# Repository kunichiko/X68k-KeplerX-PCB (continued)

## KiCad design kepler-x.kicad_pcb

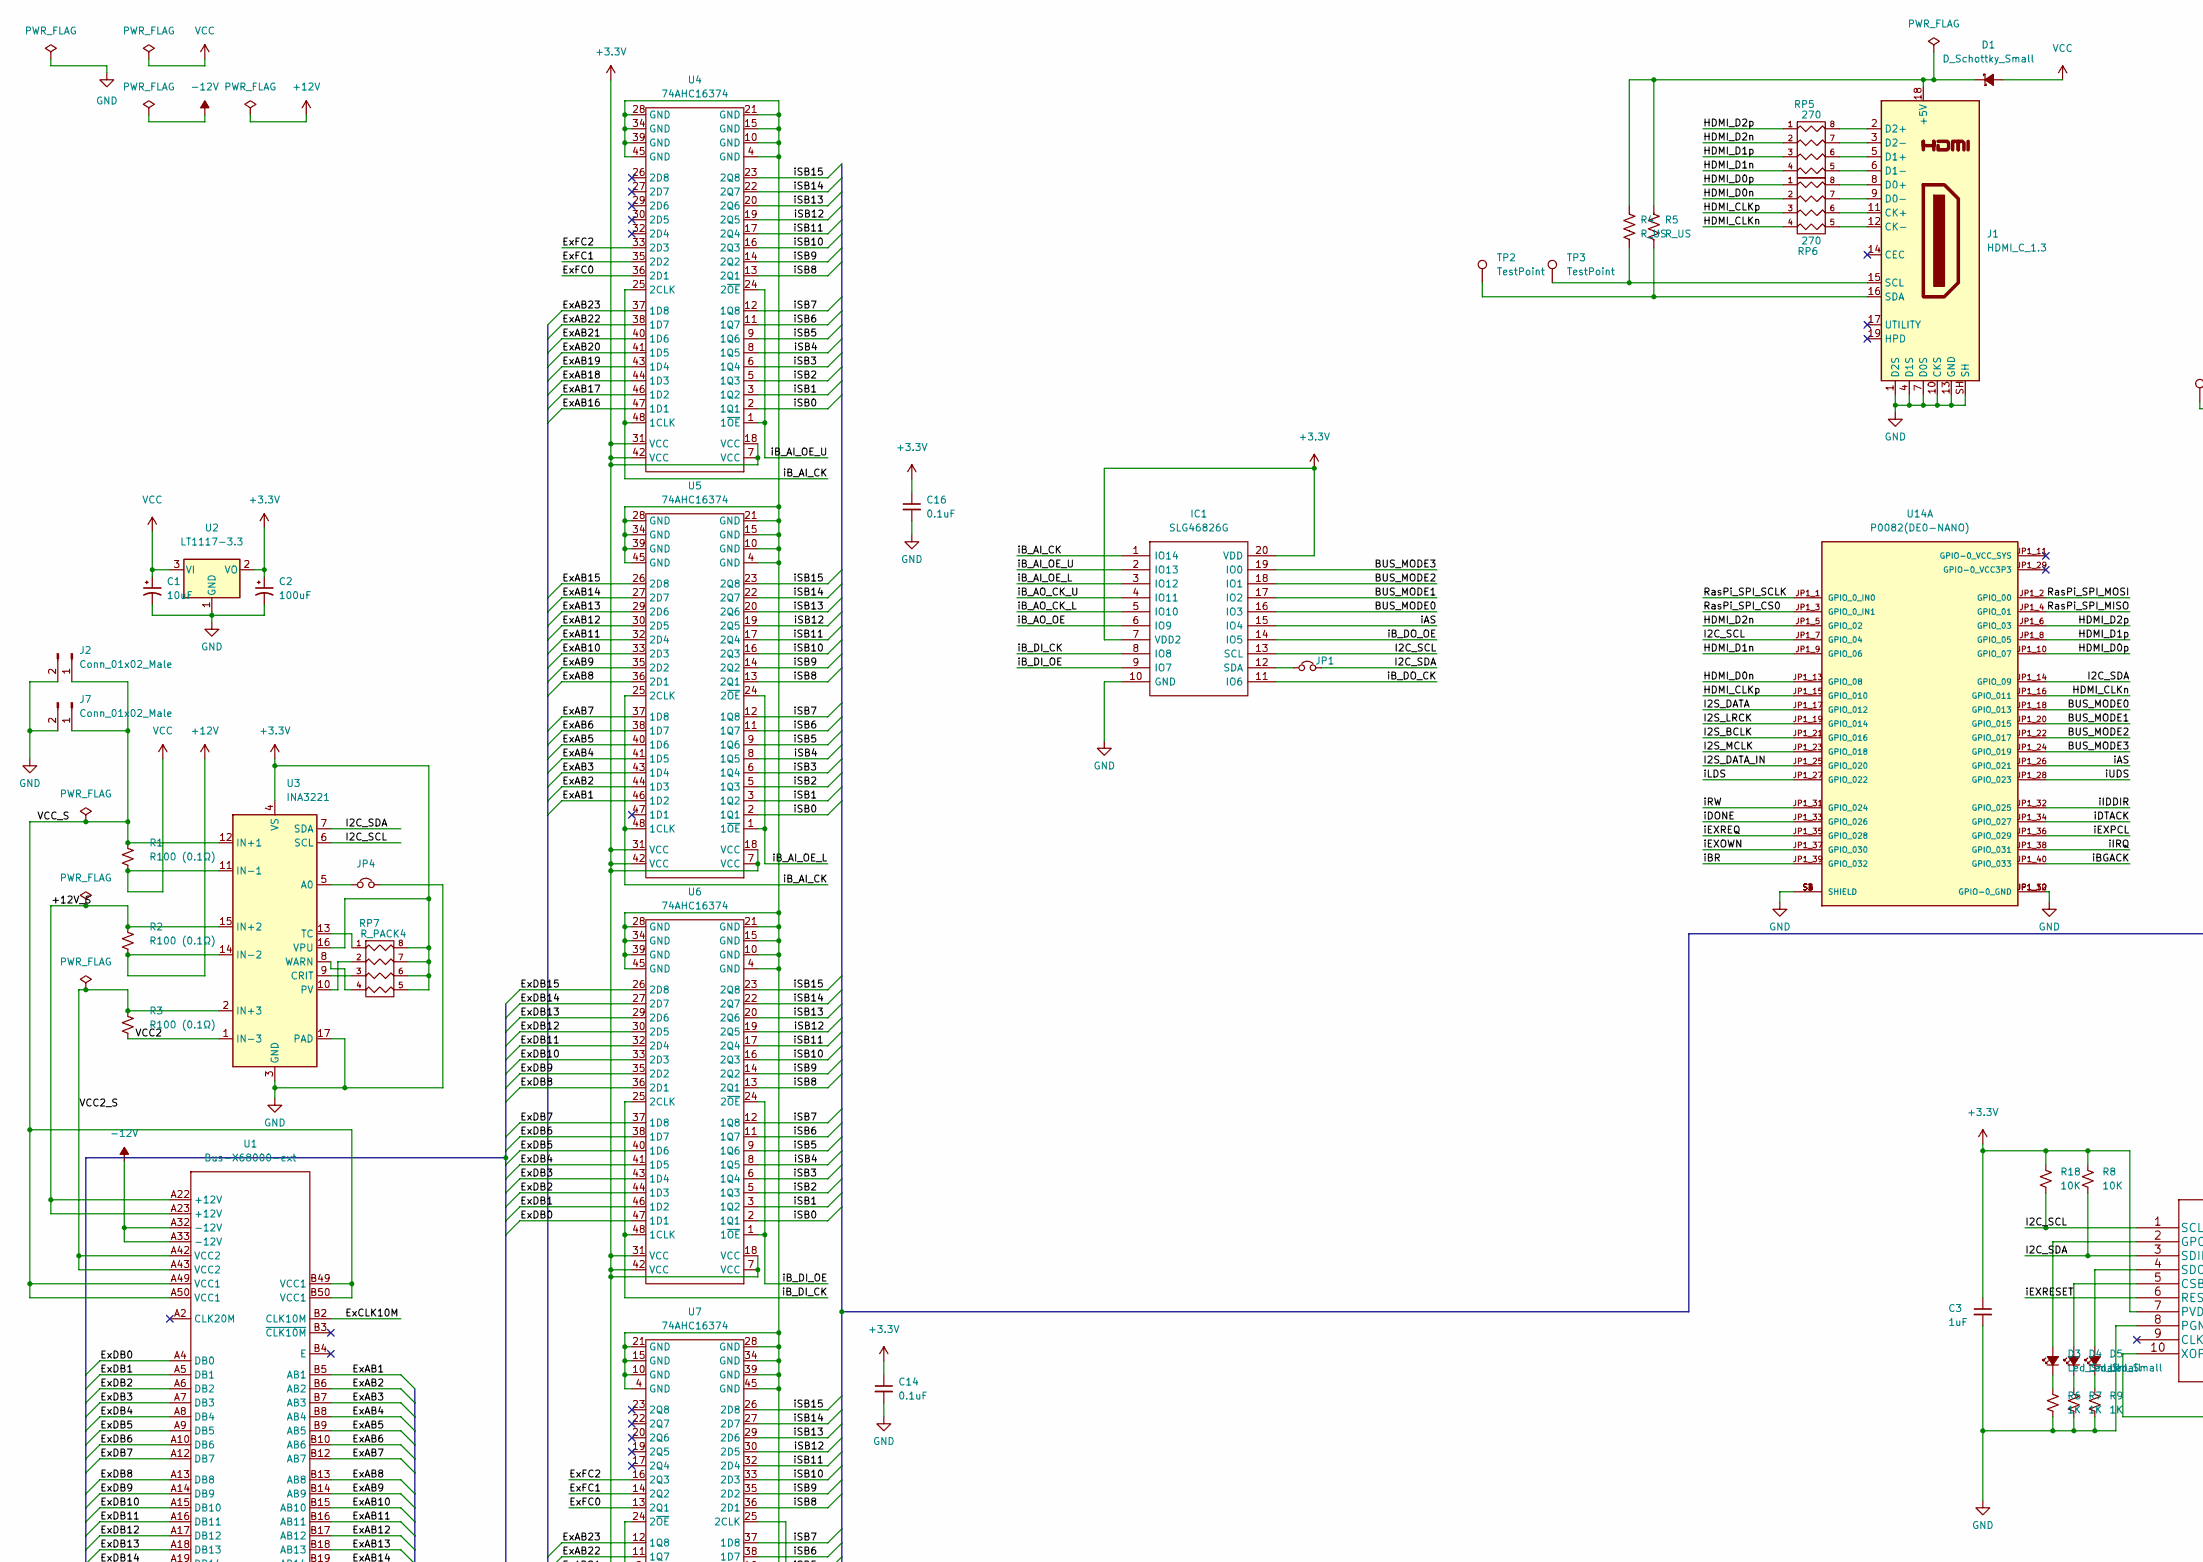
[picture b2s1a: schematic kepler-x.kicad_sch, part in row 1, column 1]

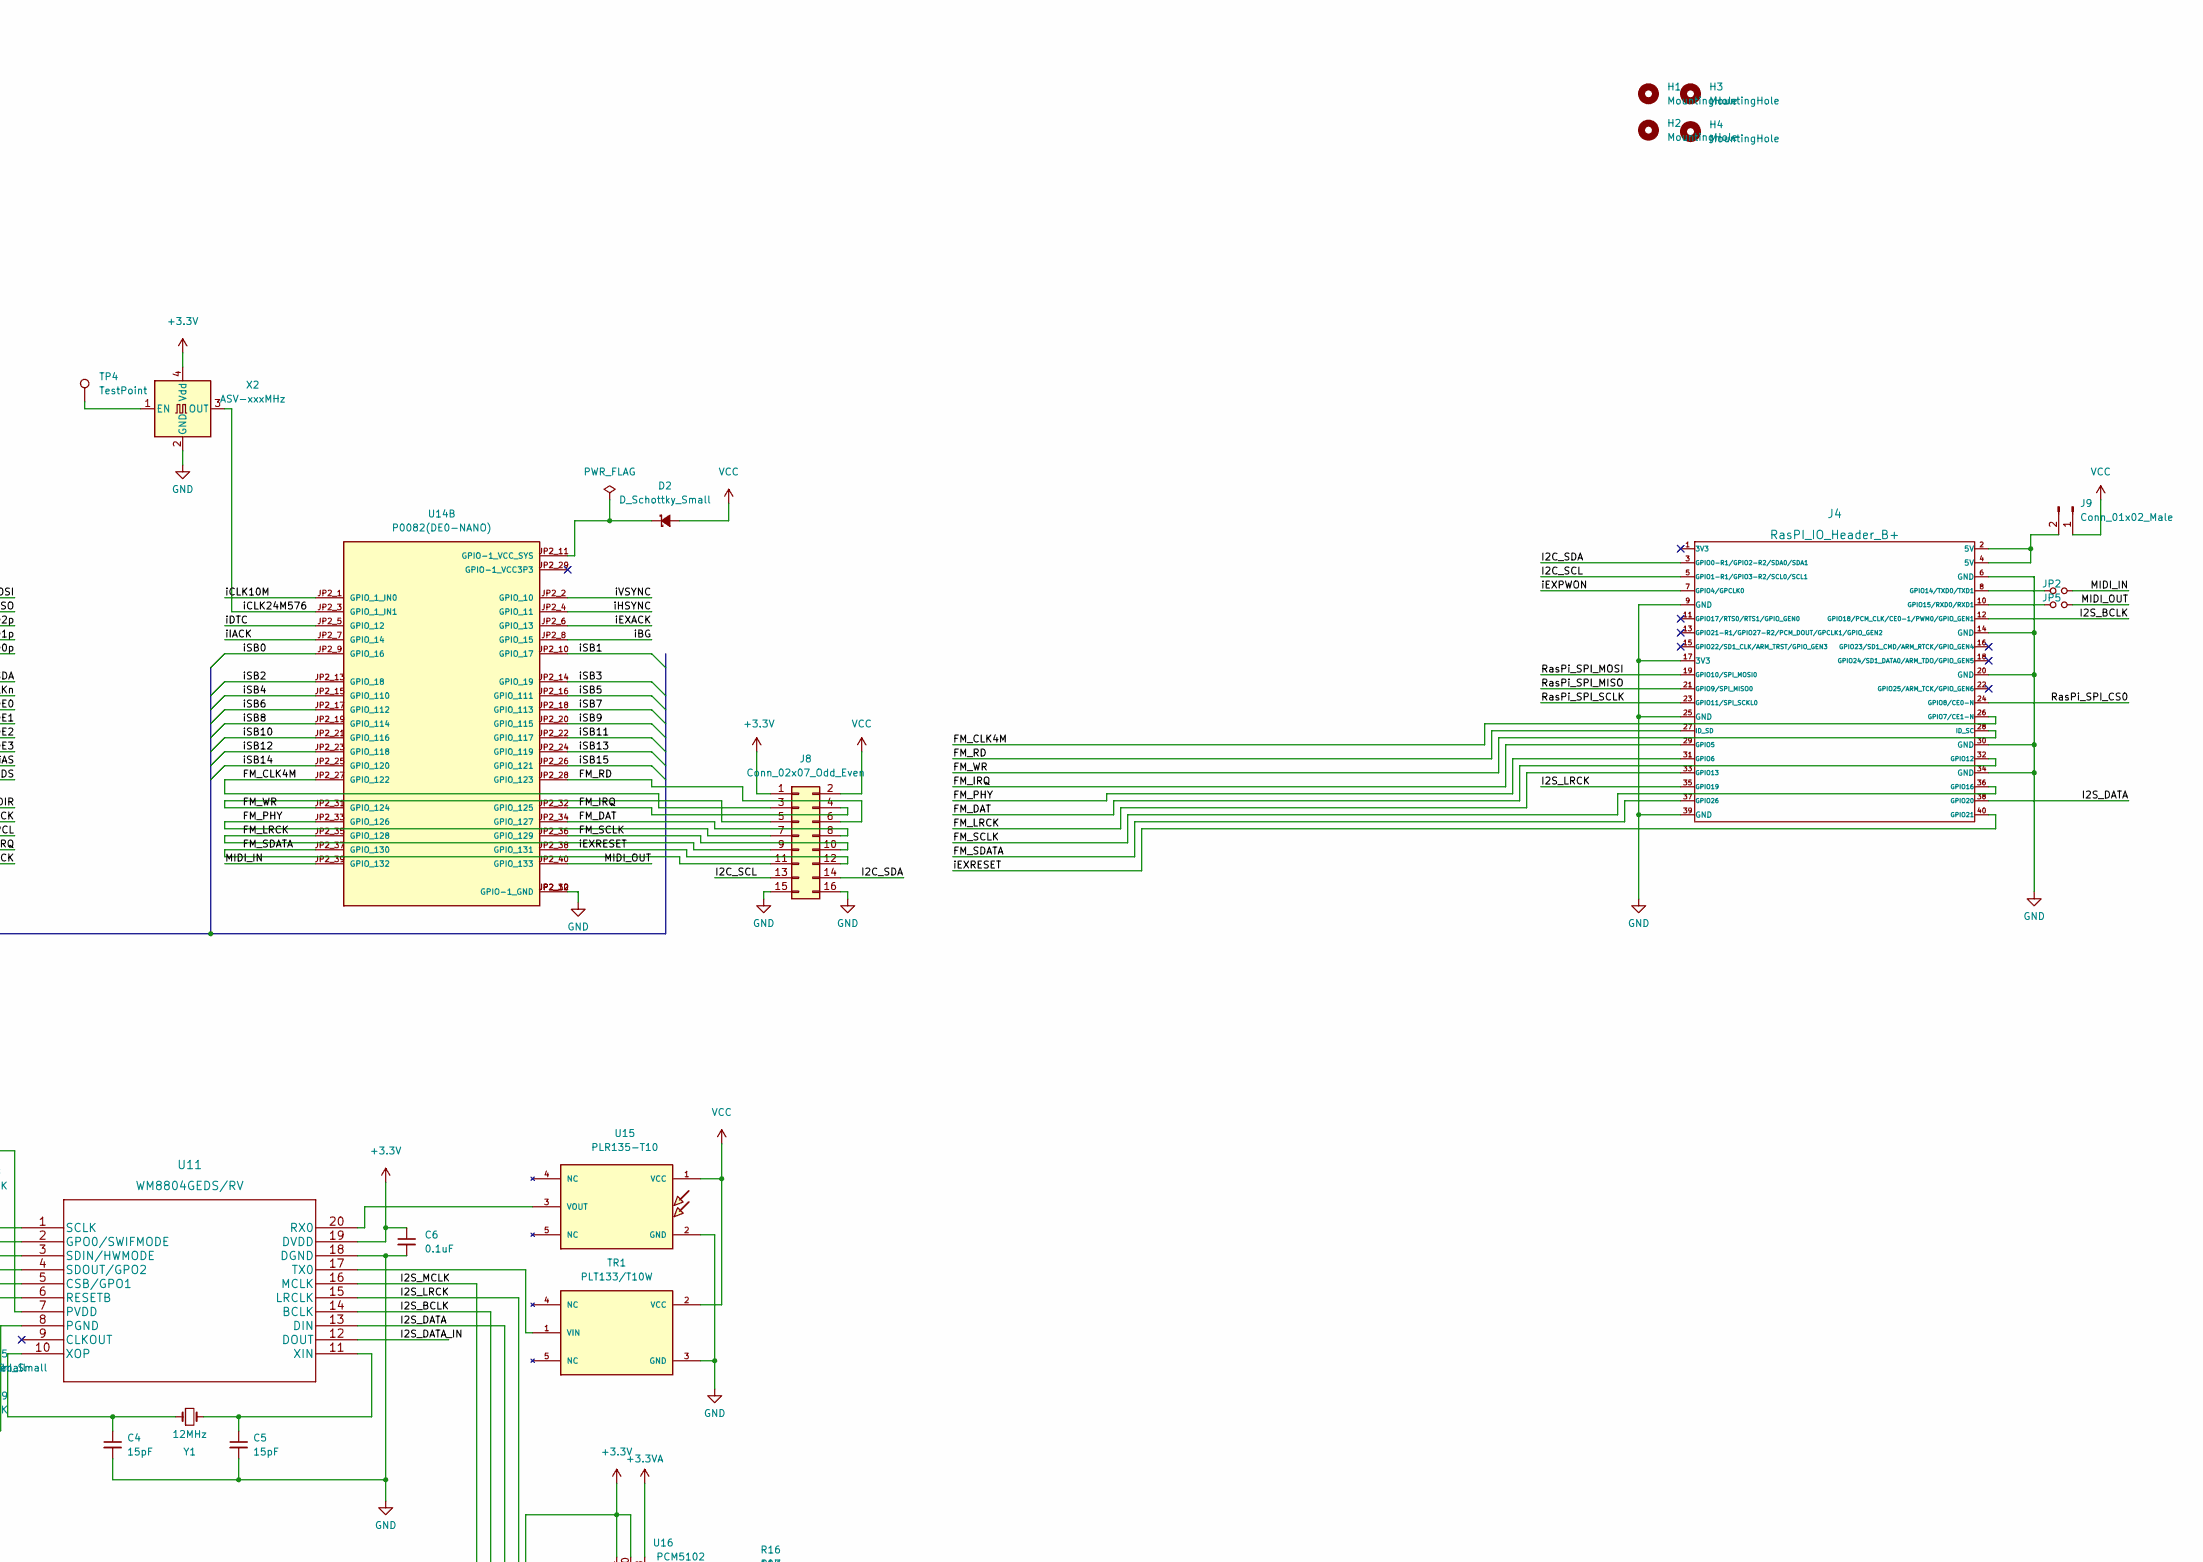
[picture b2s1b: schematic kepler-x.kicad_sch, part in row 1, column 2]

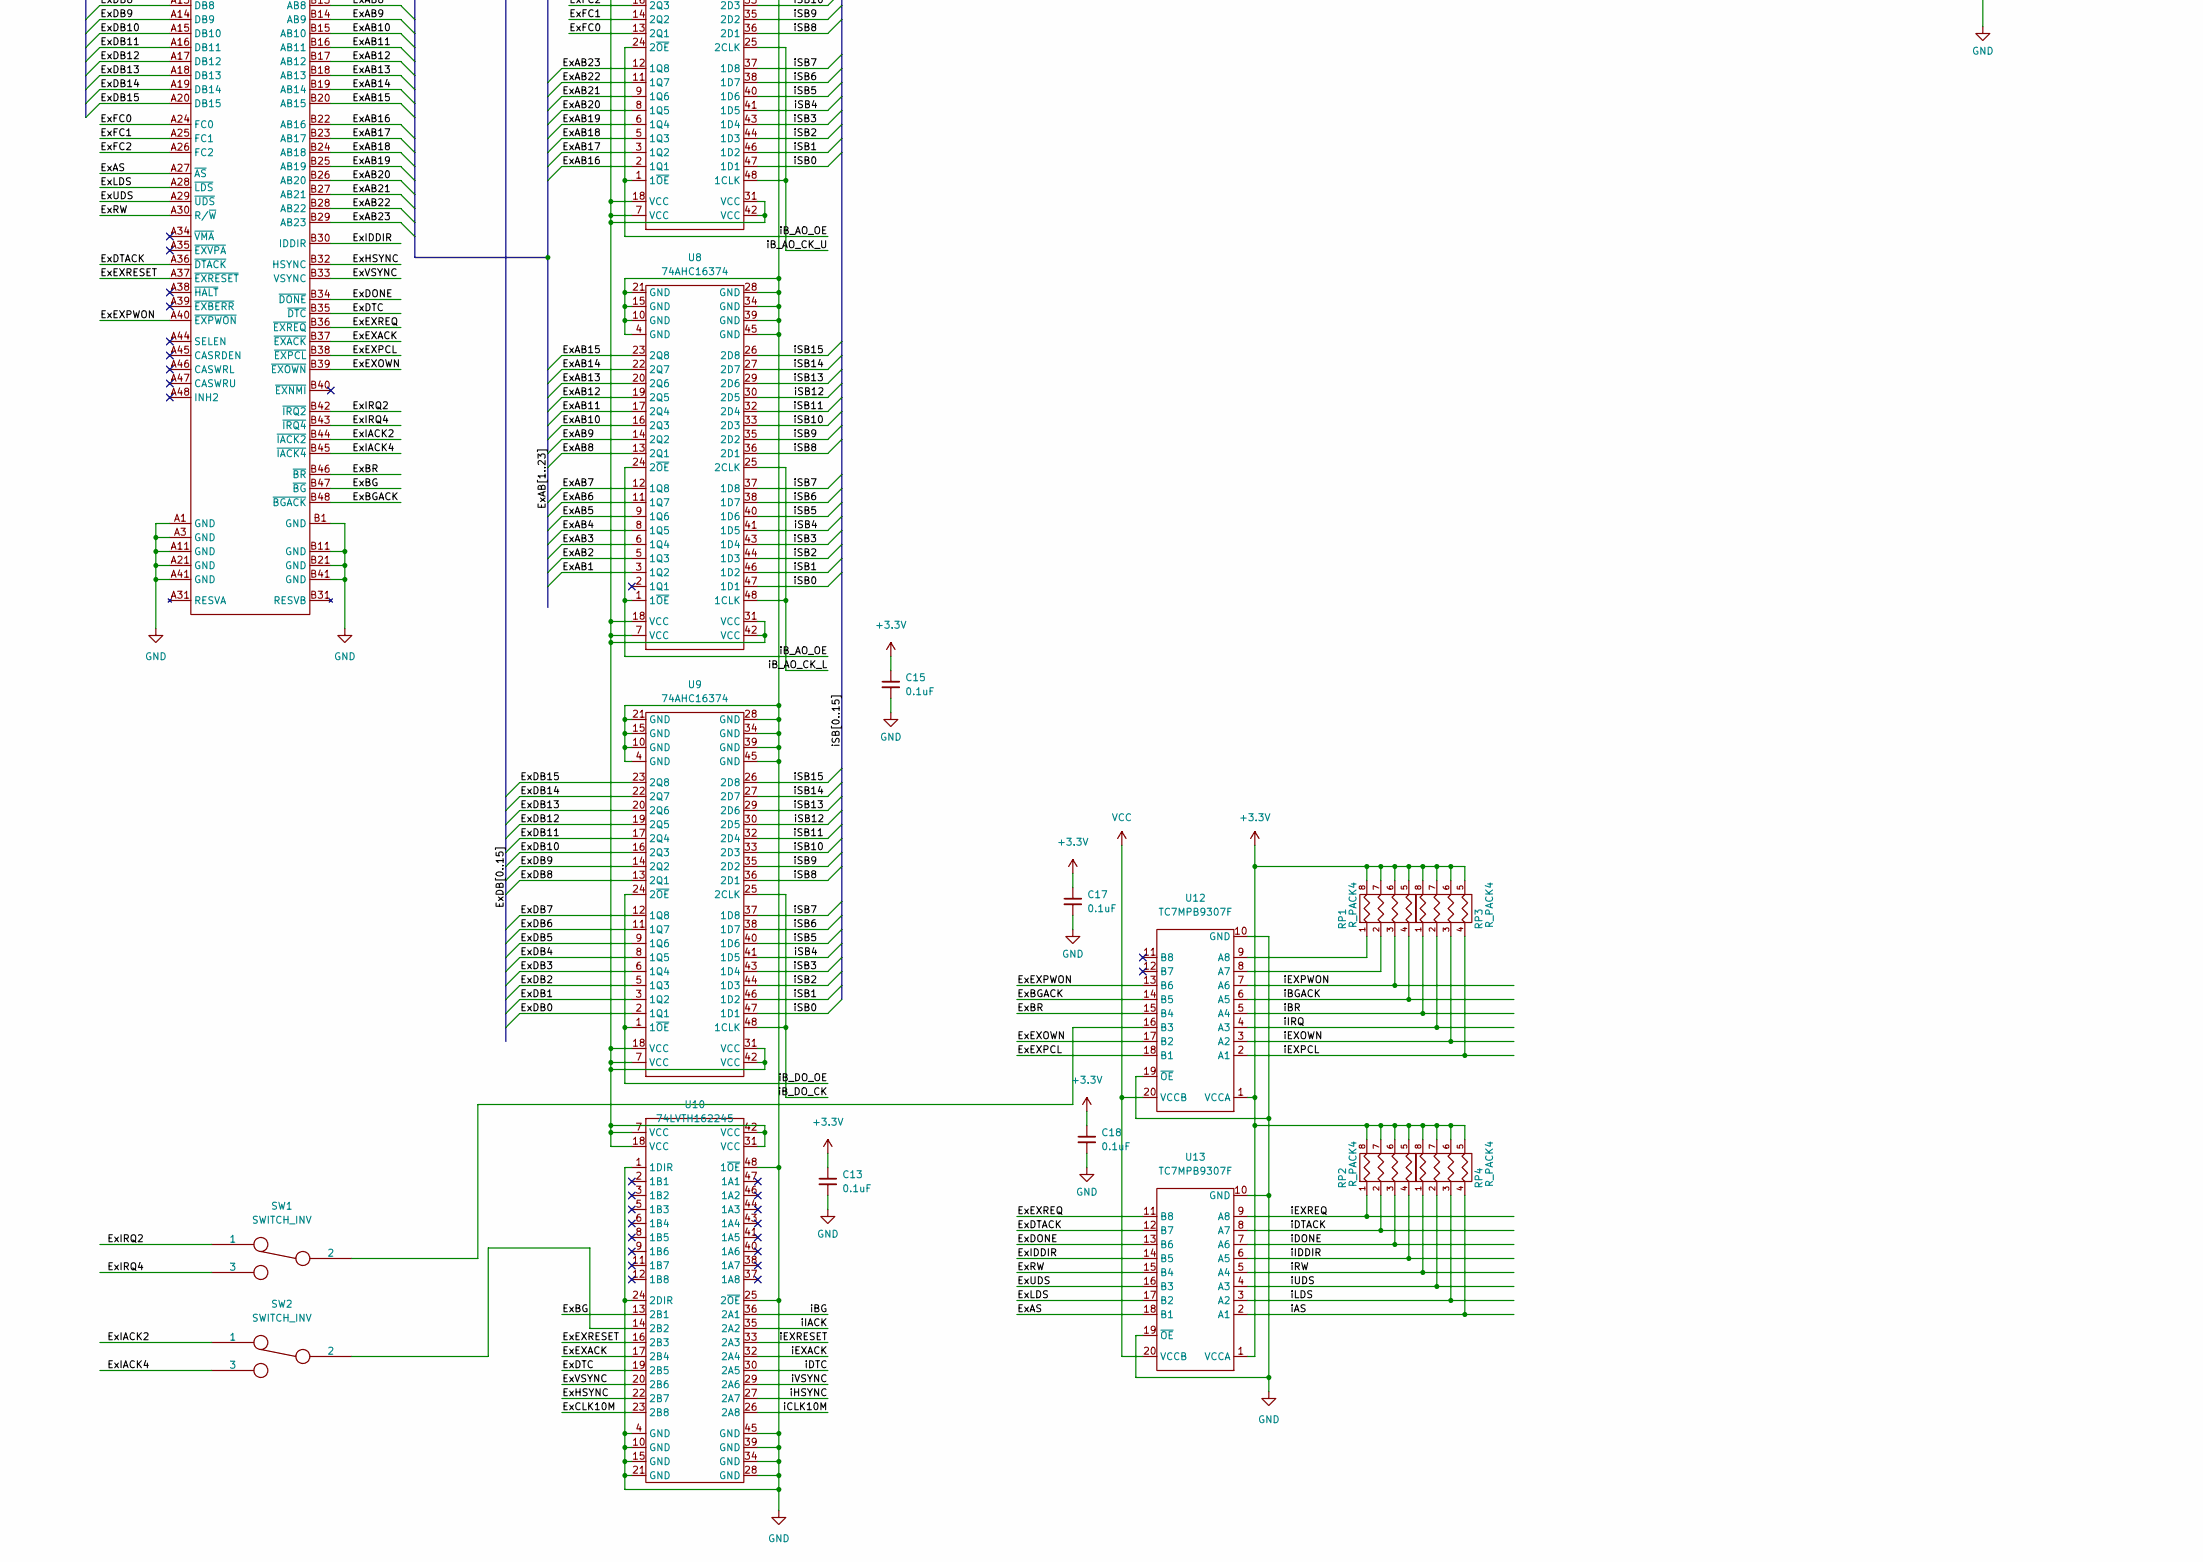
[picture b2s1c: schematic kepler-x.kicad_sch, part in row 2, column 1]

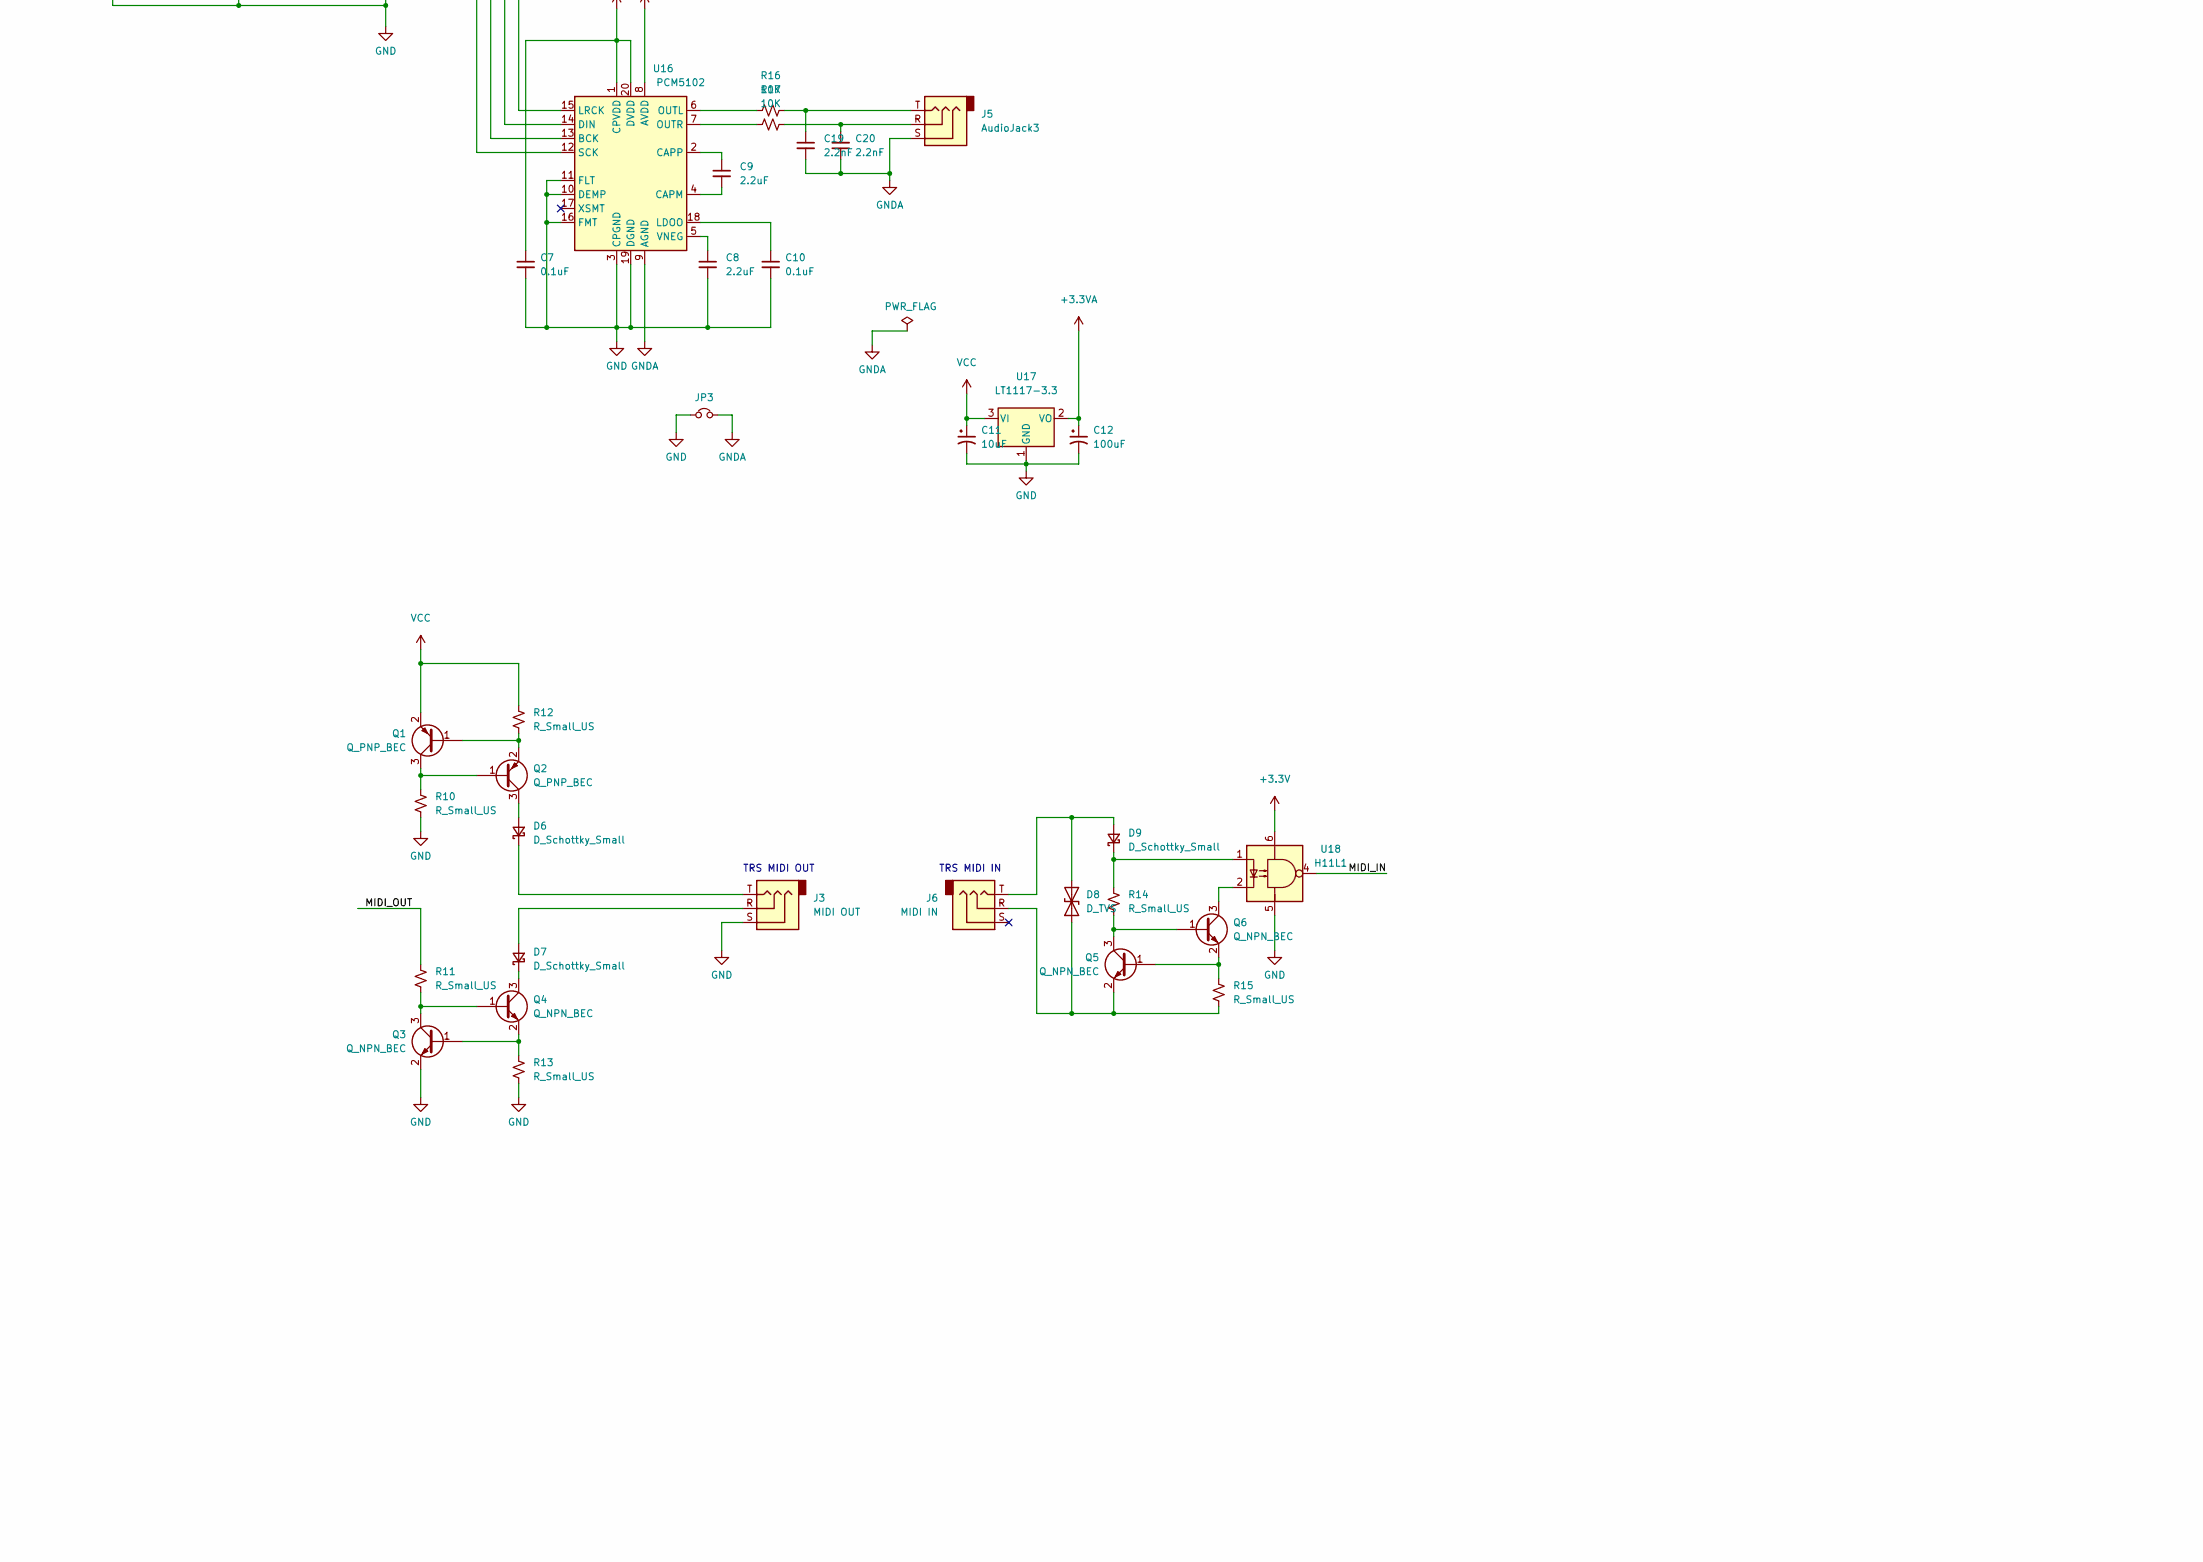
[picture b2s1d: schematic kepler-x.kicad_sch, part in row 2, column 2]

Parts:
C1, C11: 10uF; CP_Radial_D5.0mm_P2.50mm
C2, C12: 100uF; CP_Radial_D5.0mm_P2.50mm
C3: 1uF; C_0603_1608Metric_Pad1.08x0.95mm_HandSolder
C4, C5: 15pF; C_0603_1608Metric_Pad1.08x0.95mm_HandSolder
C6, C7, C10, C13, C14, C15, C16, C17, C18: 0.1uF; C_0603_1608Metric_Pad1.08x0.95mm_HandSolder
C8, C9: 2.2uF; C_0603_1608Metric_Pad1.08x0.95mm_HandSolder
C19, C20: 2.2nF; C_0603_1608Metric_Pad1.08x0.95mm_HandSolder
D1, D2, D6, D7, D9: D_Schottky_Small; D_1206_3216Metric_Pad1.42x1.75mm_HandSolder
D3, D4, D5: Led_Small; LED_0603_1608Metric_Pad1.05x0.95mm_HandSolder
D8: D_TVS; D_1206_3216Metric_Pad1.42x1.75mm_HandSolder
H1, H2: MountingHole; MountingHole_3.7mm
H3, H4: MountingHole; MountingHole_2.7mm_M2.5
IC1: SLG46826G; SOP65P640X120-20N; Manufacturer_Part_Number SLG46826G
J1: HDMI_C_1.3; HDMI_Mini_Female_2001-1-2-21-00-BK
J2, J7, J9: Conn_01x02_Male; PinHeader_1x02_P2.54mm_Vertical
J3: MIDI OUT; Jack_3.5mm_Switronic_ST-005-G_horizontal
J4: RasPI_IO_Header_B+; Raspberry_Pi_Zero_Socketed_THT_FaceDown_MountingHoles
J5: AudioJack3; Jack_3.5mm_Switronic_ST-005-G_horizontal
J6: MIDI IN; Jack_3.5mm_Switronic_ST-005-G_horizontal
J8: Conn_02x07_Odd_Even; PinHeader_2x08_P2.54mm_Vertical
JP1: Jumper_NC_Small; PinHeader_1x2_P2.54mm
JP2, JP5: Jumper_NO_Small; SolderJumper-2_P1.3mm_Open_RoundedPad1.0x1.5mm
JP3, JP4: Jumper_NC_Small; SolderJumper-2_P1.3mm_Bridged_RoundedPad1.0x1.5mm
Q1, Q2: Q_PNP_BEC; SC-59_Handsoldering
Q3, Q4, Q5, Q6: Q_NPN_BEC; SC-59_Handsoldering
R1, R2, R3: R100 (0.1Ω); R_2512_6332Metric_Pad1.40x3.35mm_HandSolder
R4, R5: R_US; R_0603_1608Metric_Pad0.98x0.95mm_HandSolder
R6, R7, R9: 1K; R_0603_1608Metric_Pad0.98x0.95mm_HandSolder
R8, R16, R17, R18: 10K; R_0603_1608Metric_Pad0.98x0.95mm_HandSolder
R10, R11, R12, R13, R14, R15: R_Small_US; R_0603_1608Metric_Pad0.98x0.95mm_HandSolder
RP1, RP2, RP3, RP4, RP7: R_PACK4; R_Array_Convex_4x0603
RP5, RP6: 270; R_Array_Convex_4x0603
SW1, SW2: SWITCH_INV; Pin_Header_Straight_1x03
TP2, TP3, TP4: TestPoint; TestPoint_THTPad_2.0x2.0mm_Drill1.0mm
TR1: PLT133/T10W; XDCR_PLT133_T10W; PARTREV 5
U1: Bus-X68000-ext; x68000-ext-cardedge
U2, U17: LT1117-3.3; SOT-223-3_TabPin2
U3: INA3221; QFN-16-1EP_4x4mm_Pitch0.65mm
U4, U5, U6, U7, U8, U9: 74AHC16374; SSOP-48_7.5x15.9mm_Pitch0.635mm
U10: 74LVTH162245; SSOP-48_7.5x15.9mm_Pitch0.635mm
U11: WM8804GEDS/RV; WM8804GEDS&slash_RV
U12, U13: TC7MPB9307F; TSSOP-20_4.4x6.5mm_Pitch0.65mm
U14: P0082(DE0-NANO); MODULE_P0082_TOPMOUNT; PARTREV V2.0
U15: PLR135-T10; XDCR_PLT133_T10W
U16: PCM5102; TSSOP-20_4.4x6.5mm_P0.65mm
U18: H11L1; DIP-6_W7.62mm
X2: ASV-xxxMHz; Oscillator_SMD_Abracon_ASV-4Pin_7.0x5.1mm
Y1: 12MHz; Crystal_HC49-U_Vertical

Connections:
+3.3VA: C12.1, U16.8 (AVDD), U17.2 (VO)
+3V3: C2.1, C3.1, C6.1, C7.1, C13.1, C14.1, C15.1, C16.1, C17.1, C18.1, IC1.7 (VDD2), IC1.20 (VDD), J8.1, R8.1, R18.1, RP1.5 (R4), RP1.6 (R3), RP1.7 (R2), RP1.8 (R1), RP2.5 (R4), RP2.6 (R3), RP2.7 (R2), RP2.8 (R1), RP3.5 (R4), RP3.6 (R3), RP3.7 (R2), RP3.8 (R1), RP4.5 (R4), RP4.6 (R3), RP4.7 (R2), RP4.8 (R1), RP7.5 (R4), RP7.6 (R3), RP7.7 (R2), RP7.8 (R1), U2.2 (VO), U3.4 (VS), U3.16 (VPU), U4.7 (VCC), U4.18 (VCC), U4.31 (VCC), U4.42 (VCC), U5.7 (VCC), U5.18 (VCC), U5.31 (VCC), U5.42 (VCC), U6.7 (VCC), U6.18 (VCC), U6.31 (VCC), U6.42 (VCC), U7.7 (VCC), U7.18 (VCC), U7.31 (VCC), U7.42 (VCC), U8.7 (VCC), U8.18 (VCC), U8.31 (VCC), U8.42 (VCC), U9.7 (VCC), U9.18 (VCC), U9.31 (VCC), U9.42 (VCC), U10.7 (VCC), U10.18 (VCC), U10.31 (VCC), U10.42 (VCC), U11.7 (PVDD), U11.19 (DVDD), U12.1 (VCCA), U13.1 (VCCA), U16.1 (CPVDD), U16.20 (DVDD), U18.6, X2.4 (Vdd)
+12V: R2.2, U3.14 (IN-2)
-12V: U1.A32 (-12V), U1.A33 (-12V)
/+12V_S: R2.1, U1.A22 (+12V), U1.A23 (+12V), U3.15 (IN+2)
/BUS_MODE0: IC1.16 (IO3), U14.JP1_18 (GPIO_013)
/BUS_MODE1: IC1.17 (IO2), U14.JP1_20 (GPIO_015)
/BUS_MODE2: IC1.18 (IO1), U14.JP1_22 (GPIO_017)
/BUS_MODE3: IC1.19 (IO0), U14.JP1_24 (GPIO_019)
/ExAB1: U1.B5 (AB1), U5.46 (1D2), U8.3 (1Q2)
/ExAB2: U1.B6 (AB2), U5.44 (1D3), U8.5 (1Q3)
/ExAB3: U1.B7 (AB3), U5.43 (1D4), U8.6 (1Q4)
/ExAB4: U1.B8 (AB4), U5.41 (1D5), U8.8 (1Q5)
/ExAB5: U1.B9 (AB5), U5.40 (1D6), U8.9 (1Q6)
/ExAB6: U1.B10 (AB6), U5.38 (1D7), U8.11 (1Q7)
/ExAB7: U1.B12 (AB7), U5.37 (1D8), U8.12 (1Q8)
/ExAB8: U1.B13 (AB8), U5.36 (2D1), U8.13 (2Q1)
/ExAB9: U1.B14 (AB9), U5.35 (2D2), U8.14 (2Q2)
/ExAB10: U1.B15 (AB10), U5.33 (2D3), U8.16 (2Q3)
/ExAB11: U1.B16 (AB11), U5.32 (2D4), U8.17 (2Q4)
/ExAB12: U1.B17 (AB12), U5.30 (2D5), U8.19 (2Q5)
/ExAB13: U1.B18 (AB13), U5.29 (2D6), U8.20 (2Q6)
/ExAB14: U1.B19 (AB14), U5.27 (2D7), U8.22 (2Q7)
/ExAB15: U1.B20 (AB15), U5.26 (2D8), U8.23 (2Q8)
/ExAB16: U1.B22 (AB16), U4.47 (1D1), U7.2 (1Q1)
/ExAB17: U1.B23 (AB17), U4.46 (1D2), U7.3 (1Q2)
/ExAB18: U1.B24 (AB18), U4.44 (1D3), U7.5 (1Q3)
/ExAB19: U1.B25 (AB19), U4.43 (1D4), U7.6 (1Q4)
/ExAB20: U1.B26 (AB20), U4.41 (1D5), U7.8 (1Q5)
/ExAB21: U1.B27 (AB21), U4.40 (1D6), U7.9 (1Q6)
/ExAB22: U1.B28 (AB22), U4.38 (1D7), U7.11 (1Q7)
/ExAB23: U1.B29 (AB23), U4.37 (1D8), U7.12 (1Q8)
/ExAS: U1.A27 (~AS), U13.18 (B1)
/ExBG: U1.B47 (~BG), U10.13 (2B1)
/ExBGACK: U1.B48 (~BGACK), U12.14 (B5)
/ExBR: U1.B46 (~BR), U12.15 (B4)
/ExCLK10M: U1.B2 (CLK10M), U10.23 (2B8)
/ExDB0: U1.A4 (DB0), U6.47 (1D1), U9.2 (1Q1)
/ExDB1: U1.A5 (DB1), U6.46 (1D2), U9.3 (1Q2)
/ExDB2: U1.A6 (DB2), U6.44 (1D3), U9.5 (1Q3)
/ExDB3: U1.A7 (DB3), U6.43 (1D4), U9.6 (1Q4)
/ExDB4: U1.A8 (DB4), U6.41 (1D5), U9.8 (1Q5)
/ExDB5: U1.A9 (DB5), U6.40 (1D6), U9.9 (1Q6)
/ExDB6: U1.A10 (DB6), U6.38 (1D7), U9.11 (1Q7)
/ExDB7: U1.A12 (DB7), U6.37 (1D8), U9.12 (1Q8)
/ExDB8: U1.A13 (DB8), U6.36 (2D1), U9.13 (2Q1)
/ExDB9: U1.A14 (DB9), U6.35 (2D2), U9.14 (2Q2)
/ExDB10: U1.A15 (DB10), U6.33 (2D3), U9.16 (2Q3)
/ExDB11: U1.A16 (DB11), U6.32 (2D4), U9.17 (2Q4)
/ExDB12: U1.A17 (DB12), U6.30 (2D5), U9.19 (2Q5)
/ExDB13: U1.A18 (DB13), U6.29 (2D6), U9.20 (2Q6)
/ExDB14: U1.A19 (DB14), U6.27 (2D7), U9.22 (2Q7)
/ExDB15: U1.A20 (DB15), U6.26 (2D8), U9.23 (2Q8)
/ExDONE: U1.B34 (~DONE), U13.13 (B6)
/ExDTACK: U1.A36 (~DTACK), U13.12 (B7)
/ExDTC: U1.B35 (~DTC), U10.19 (2B5)
/ExEXACK: U1.B37 (~EXACK), U10.17 (2B4)
/ExEXOWN: U1.B39 (~EXOWN), U12.17 (B2)
/ExEXPCL: U1.B38 (~EXPCL), U12.18 (B1)
/ExEXPWON: U1.A40 (~EXPWON), U12.13 (B6)
/ExEXREQ: U1.B36 (~EXREQ), U13.11 (B8)
/ExEXRESET: U1.A37 (~EXRESET), U10.16 (2B3)
/ExFC0: U1.A24 (FC0), U4.36 (2D1), U7.13 (2Q1)
/ExFC1: U1.A25 (FC1), U4.35 (2D2), U7.14 (2Q2)
/ExFC2: U1.A26 (FC2), U4.33 (2D3), U7.16 (2Q3)
/ExHSYNC: U1.B32 (HSYNC), U10.22 (2B7)
/ExIACK2: SW2.1, U1.B44 (~IACK2)
/ExIACK4: SW2.3, U1.B45 (~IACK4)
/ExIDDIR: U1.B30 (IDDIR), U13.14 (B5)
/ExIRQ2: SW1.1, U1.B42 (~IRQ2)
/ExIRQ4: SW1.3, U1.B43 (~IRQ4)
/ExLDS: U1.A28 (~LDS), U13.17 (B2)
/ExRW: U1.A30 (R/~W), U13.15 (B4)
/ExUDS: U1.A29 (~UDS), U13.16 (B3)
/ExVSYNC: U1.B33 (VSYNC), U10.20 (2B6)
/FM_CLK4M: J4.26 (GPIO7/CE1-N), J8.3, U14.JP2_27 (GPIO_122)
/FM_DAT: J4.32 (GPIO12), J8.8, U14.JP2_34 (GPIO_127)
/FM_IRQ: J4.29 (GPIO5), J8.4, U14.JP2_32 (GPIO_125)
/FM_LRCK: J4.33 (GPIO13), J8.9, U14.JP2_35 (GPIO_128)
/FM_PHY: J4.31 (GPIO6), J8.7, U14.JP2_33 (GPIO_126)
/FM_RD: J4.27 (ID_SD), J8.6, U14.JP2_28 (GPIO_123)
/FM_SCLK: J4.36 (GPIO16), J8.10, U14.JP2_36 (GPIO_129)
/FM_SDATA: J4.37 (GPIO26), J8.11, U14.JP2_37 (GPIO_130)
/FM_WR: J4.28 (ID_SC), J8.5, U14.JP2_31 (GPIO_124)
/HDMI_CLKn: RP6.4, U14.JP1_16 (GPIO_011)
/HDMI_CLKp: RP6.3, U14.JP1_15 (GPIO_010)
/HDMI_D0n: RP6.2, U14.JP1_13 (GPIO_08)
/HDMI_D0p: RP6.1, U14.JP1_10 (GPIO_07)
/HDMI_D1n: RP5.4, U14.JP1_9 (GPIO_06)
/HDMI_D1p: RP5.3, U14.JP1_8 (GPIO_05)
/HDMI_D2n: RP5.2, U14.JP1_5 (GPIO_02)
/HDMI_D2p: RP5.1, U14.JP1_6 (GPIO_03)
/I2C_SCL: IC1.13 (SCL), J4.5 (GPIO1-R1/GPIO3-R2/SCL0/SCL1), J8.13, R18.2, U3.6 (SCL), U11.1 (SCLK), U14.JP1_7 (GPIO_04)
/I2C_SDA: J4.3 (GPIO0-R1/GPIO2-R2/SDA0/SDA1), J8.14, JP1.2, R8.2, U3.7 (SDA), U11.3 (SDIN/HWMODE), U14.JP1_14 (GPIO_09)
/I2S_BCLK: J4.12 (GPIO18/PCM_CLK/CE0-1/PWM0/GPIO_GEN1), U11.14 (BCLK), U14.JP1_21 (GPIO_016), U16.13 (BCK)
/I2S_DATA: J4.38 (GPIO20), U11.13 (DIN), U14.JP1_17 (GPIO_012), U16.14 (DIN)
/I2S_DATA_IN: U11.12 (DOUT), U14.JP1_25 (GPIO_020)
/I2S_LRCK: J4.35 (GPIO19), U11.15 (LRCLK), U14.JP1_19 (GPIO_014), U16.15 (LRCK)
/I2S_MCLK: U11.16 (MCLK), U14.JP1_23 (GPIO_018), U16.12 (SCK)
/MIDI_IN: JP2.2, U14.JP2_39 (GPIO_132), U18.4
/MIDI_OUT: JP5.2, R11.1, U14.JP2_40 (GPIO_133)
/RasPi_SPI_CS0: J4.24 (GPIO8/CE0-N), U14.JP1_3 (GPIO_0_IN1)
/RasPi_SPI_MISO: J4.21 (GPIO9/SPI_MISO0), U14.JP1_4 (GPIO_01)
/RasPi_SPI_MOSI: J4.19 (GPIO10/SPI_MOSI0), U14.JP1_2 (GPIO_00)
/RasPi_SPI_SCLK: J4.23 (GPIO11/SPI_SCKL0), U14.JP1_1 (GPIO_0_IN0)
/VCC2: R3.2, U3.1 (IN-3)
/VCC2_S: R3.1, U1.A42 (VCC2), U1.A43 (VCC2), U3.2 (IN+3)
/VCC_S: J2.1, J7.1, R1.1, U1.A49 (VCC1), U1.A50 (VCC1), U1.B49 (VCC1), U1.B50 (VCC1), U3.12 (IN+1)
/iAS: IC1.15 (IO4), RP4.4, U13.2 (A1), U14.JP1_26 (GPIO_021)
/iBG: U10.36 (2A1), U14.JP2_8 (GPIO_15)
/iBGACK: RP1.4, U12.6 (A5), U14.JP1_40 (GPIO_033)
/iBR: RP3.1, U12.5 (A4), U14.JP1_39 (GPIO_032)
/iB_AI_CK: IC1.1 (IO14), U4.25 (2CLK), U4.48 (1CLK), U5.25 (2CLK), U5.48 (1CLK)
/iB_AI_OE_L: IC1.3 (IO12), U5.1 (1~OE), U5.24 (2~OE)
/iB_AI_OE_U: IC1.2 (IO13), U4.1 (1~OE), U4.24 (2~OE)
/iB_AO_CK_L: IC1.5 (IO10), U8.25 (2CLK), U8.48 (1CLK)
/iB_AO_CK_U: IC1.4 (IO11), U7.25 (2CLK), U7.48 (1CLK)
/iB_AO_OE: IC1.6 (IO9), U7.1 (1~OE), U7.24 (2~OE), U8.1 (1~OE), U8.24 (2~OE)
/iB_DI_CK: IC1.8 (IO8), U6.25 (2CLK), U6.48 (1CLK)
/iB_DI_OE: IC1.9 (IO7), U6.1 (1~OE), U6.24 (2~OE)
/iB_DO_CK: IC1.11 (IO6), U9.25 (2CLK), U9.48 (1CLK)
/iB_DO_OE: IC1.14 (IO5), U9.1 (1~OE), U9.24 (2~OE)
/iCLK10M: U10.26 (2A8), U14.JP2_1 (GPIO_1_IN0)
/iCLK24M576: U14.JP2_3 (GPIO_1_IN1), X2.3 (OUT)
/iDONE: RP2.3, U13.7 (A6), U14.JP1_33 (GPIO_026)
/iDTACK: RP2.2, U13.8 (A7), U14.JP1_34 (GPIO_027)
/iDTC: U10.30 (2A5), U14.JP2_5 (GPIO_12)
/iEXACK: U10.32 (2A4), U14.JP2_6 (GPIO_13)
/iEXOWN: RP3.3, U12.3 (A2), U14.JP1_37 (GPIO_030)
/iEXPCL: RP3.4, U12.2 (A1), U14.JP1_36 (GPIO_029)
/iEXPWON: J4.7 (GPIO4/GPCLK0), RP1.3, U12.7 (A6)
/iEXREQ: RP2.1, U13.9 (A8), U14.JP1_35 (GPIO_028)
/iEXRESET: J4.40 (GPIO21), J8.12, U10.33 (2A3), U11.6 (RESETB), U14.JP2_38 (GPIO_131)
/iHSYNC: U10.27 (2A7), U14.JP2_4 (GPIO_11)
/iIACK: U10.35 (2A2), U14.JP2_7 (GPIO_14)
/iIDDIR: RP2.4, U13.6 (A5), U14.JP1_32 (GPIO_025)
/iIRQ: RP3.2, U12.4 (A3), U14.JP1_38 (GPIO_031)
/iLDS: RP4.3, U13.3 (A2), U14.JP1_27 (GPIO_022)
/iRW: RP4.1, U13.5 (A4), U14.JP1_31 (GPIO_024)
/iSB0: U4.2 (1Q1), U5.2 (1Q1), U6.2 (1Q1), U7.47 (1D1), U8.47 (1D1), U9.47 (1D1), U14.JP2_9 (GPIO_16)
/iSB1: U4.3 (1Q2), U5.3 (1Q2), U6.3 (1Q2), U7.46 (1D2), U8.46 (1D2), U9.46 (1D2), U14.JP2_10 (GPIO_17)
/iSB2: U4.5 (1Q3), U5.5 (1Q3), U6.5 (1Q3), U7.44 (1D3), U8.44 (1D3), U9.44 (1D3), U14.JP2_13 (GPIO_18)
/iSB3: U4.6 (1Q4), U5.6 (1Q4), U6.6 (1Q4), U7.43 (1D4), U8.43 (1D4), U9.43 (1D4), U14.JP2_14 (GPIO_19)
/iSB4: U4.8 (1Q5), U5.8 (1Q5), U6.8 (1Q5), U7.41 (1D5), U8.41 (1D5), U9.41 (1D5), U14.JP2_15 (GPIO_110)
/iSB5: U4.9 (1Q6), U5.9 (1Q6), U6.9 (1Q6), U7.40 (1D6), U8.40 (1D6), U9.40 (1D6), U14.JP2_16 (GPIO_111)
/iSB6: U4.11 (1Q7), U5.11 (1Q7), U6.11 (1Q7), U7.38 (1D7), U8.38 (1D7), U9.38 (1D7), U14.JP2_17 (GPIO_112)
/iSB7: U4.12 (1Q8), U5.12 (1Q8), U6.12 (1Q8), U7.37 (1D8), U8.37 (1D8), U9.37 (1D8), U14.JP2_18 (GPIO_113)
/iSB8: U4.13 (2Q1), U5.13 (2Q1), U6.13 (2Q1), U7.36 (2D1), U8.36 (2D1), U9.36 (2D1), U14.JP2_19 (GPIO_114)
/iSB9: U4.14 (2Q2), U5.14 (2Q2), U6.14 (2Q2), U7.35 (2D2), U8.35 (2D2), U9.35 (2D2), U14.JP2_20 (GPIO_115)
/iSB10: U4.16 (2Q3), U5.16 (2Q3), U6.16 (2Q3), U7.33 (2D3), U8.33 (2D3), U9.33 (2D3), U14.JP2_21 (GPIO_116)
/iSB11: U4.17 (2Q4), U5.17 (2Q4), U6.17 (2Q4), U7.32 (2D4), U8.32 (2D4), U9.32 (2D4), U14.JP2_22 (GPIO_117)
/iSB12: U4.19 (2Q5), U5.19 (2Q5), U6.19 (2Q5), U7.30 (2D5), U8.30 (2D5), U9.30 (2D5), U14.JP2_23 (GPIO_118)
/iSB13: U4.20 (2Q6), U5.20 (2Q6), U6.20 (2Q6), U7.29 (2D6), U8.29 (2D6), U9.29 (2D6), U14.JP2_24 (GPIO_119)
/iSB14: U4.22 (2Q7), U5.22 (2Q7), U6.22 (2Q7), U7.27 (2D7), U8.27 (2D7), U9.27 (2D7), U14.JP2_25 (GPIO_120)
/iSB15: U4.23 (2Q8), U5.23 (2Q8), U6.23 (2Q8), U7.26 (2D8), U8.26 (2D8), U9.26 (2D8), U14.JP2_26 (GPIO_121)
/iUDS: RP4.2, U13.4 (A3), U14.JP1_28 (GPIO_023)
/iVSYNC: U10.29 (2A6), U14.JP2_2 (GPIO_10)
GND: C1.2, C2.2, C3.2, C4.2, C5.2, C6.2, C7.2, C8.2, C10.2, C11.2, C12.2, C13.2, C14.2, C15.2, C16.2, C17.2, C18.2, IC1.10 (GND), J1.1 (D2S), J1.4 (D1S), J1.7 (D0S), J1.10 (CKS), J1.13 (GND), J1.SH, J2.2, J3.S, J4.6 (GND), J4.9 (GND), J4.14 (GND), J4.17 (3V3), J4.20 (GND), J4.25 (GND), J4.30 (GND), J4.34 (GND), J4.39 (GND), J7.2, J8.15, J8.16, JP3.1, JP4.2, Q3.2 (E), R6.2, R7.2, R9.2, R10.2, R13.2, TR1.3 (GND), U1.A1 (GND), U1.A3 (GND), U1.A11 (GND), U1.A21 (GND), U1.A41 (GND), U1.B1 (GND), U1.B11 (GND), U1.B21 (GND), U1.B41 (GND), U2.1 (GND), U3.3 (GND), U3.17 (PAD), U4.4 (GND), U4.10 (GND), U4.15 (GND), U4.21 (GND), U4.28 (GND), U4.34 (GND), U4.39 (GND), U4.45 (GND), U5.4 (GND), U5.10 (GND), U5.15 (GND), U5.21 (GND), U5.28 (GND), U5.34 (GND), U5.39 (GND), U5.45 (GND), U6.4 (GND), U6.10 (GND), U6.15 (GND), U6.21 (GND), U6.28 (GND), U6.34 (GND), U6.39 (GND), U6.45 (GND), U7.4 (GND), U7.10 (GND), U7.15 (GND), U7.21 (GND), U7.28 (GND), U7.34 (GND), U7.39 (GND), U7.45 (GND), U8.4 (GND), U8.10 (GND), U8.15 (GND), U8.21 (GND), U8.28 (GND), U8.34 (GND), U8.39 (GND), U8.45 (GND), U9.4 (GND), U9.10 (GND), U9.15 (GND), U9.21 (GND), U9.28 (GND), U9.34 (GND), U9.39 (GND), U9.45 (GND), U10.1 (1DIR), U10.4 (GND), U10.10 (GND), U10.15 (GND), U10.21 (GND), U10.24 (2DIR), U10.25 (2~OE), U10.28 (GND), U10.34 (GND), U10.39 (GND), U10.45 (GND), U10.48 (1~OE), U11.8 (PGND), U11.18 (DGND), U12.10 (GND), U12.19 (~OE), U13.10 (GND), U13.19 (~OE), U14.JP1_12 (GPIO-0_GND), U14.JP1_30 (GPIO-0_GND), U14.JP2_12 (GPIO-1_GND), U14.JP2_30 (GPIO-1_GND), U14.S1 (SHIELD), U14.S2 (SHIELD), U14.S3 (SHIELD), U14.S4 (SHIELD), U15.2 (GND), U16.3 (CPGND), U16.10 (DEMP), U16.11 (FLT), U16.16 (FMT), U16.19 (DGND), U17.1 (GND), U18.5, X2.2 (GND)
GNDA: C19.2, C20.1, J5.S, JP3.2, U16.9 (AGND)
unnamed: C4.1, U11.10 (XOP), Y1.1
unnamed: C5.1, U11.11 (XIN), Y1.2
unnamed: C8.1, U16.5 (VNEG)
unnamed: C9.1, U16.2 (CAPP)
unnamed: C9.2, U16.4 (CAPM)
unnamed: C10.1, U16.18 (LDOO)
unnamed: D1.1 (K), J1.18 (+5V), R4.1, R5.1
unnamed: D2.1 (K), U14.JP2_11 (GPIO-1_VCC_SYS)
unnamed: D3.1 (K), R6.1
unnamed: D3.2 (A), U11.2 (GPO0/SWIFMODE)
unnamed: D4.1 (K), R7.1
unnamed: D4.2 (A), U11.5 (CSB/GPO1)
unnamed: D5.1 (K), R9.1
unnamed: D5.2 (A), U11.4 (SDOUT/GPO2)
unnamed: D6.1 (K), J3.T
unnamed: D6.2 (A), Q2.3 (C)
unnamed: D7.1 (K), Q4.3 (C)
unnamed: D7.2 (A), J3.R
unnamed: D8.1 (A1), J6.R, Q5.2 (E), R15.2
unnamed: D8.2 (A2), D9.2 (A), J6.T
unnamed: D9.1 (K), R14.1, U18.1
unnamed: IC1.12 (SDA), JP1.1
unnamed: J1.2 (D2+), RP5.8 (R1)
unnamed: J1.3 (D2-), RP5.7 (R2)
unnamed: J1.5 (D1+), RP5.6 (R3)
unnamed: J1.6 (D1-), RP5.5 (R4)
unnamed: J1.8 (D0+), RP6.8 (R1)
unnamed: J1.9 (D0-), RP6.7 (R2)
unnamed: J1.11 (CK+), RP6.6 (R3)
unnamed: J1.12 (CK-), RP6.5 (R4)
unnamed: J1.15 (SCL), R4.2, TP3.1
unnamed: J1.16 (SDA), R5.2, TP2.1
unnamed: J4.2 (5V), J4.4 (5V), J9.2
unnamed: J4.8 (GPIO14/TXD0/TXD1), JP2.1
unnamed: J4.10 (GPIO15/RXD0/RXD1), JP5.1
unnamed: C20.2, J5.R, R17.2
unnamed: C19.1, J5.T, R16.2
unnamed: JP4.1, U3.5 (A0)
unnamed: Q1.1 (B), Q2.2 (E), R12.2
unnamed: Q1.3 (C), Q2.1 (B), R10.1
unnamed: Q3.1 (B), Q4.2 (E), R13.1
unnamed: Q3.3 (C), Q4.1 (B), R11.2
unnamed: Q5.1 (B), Q6.2 (E), R15.1
unnamed: Q5.3 (C), Q6.1 (B), R14.2
unnamed: Q6.3 (C), U18.2
unnamed: RP1.1, U12.9 (A8)
unnamed: RP1.2, U12.8 (A7)
unnamed: RP7.1, U3.13 (TC)
unnamed: RP7.2, U3.10 (PV)
unnamed: RP7.3, U3.9 (CRIT)
unnamed: RP7.4, U3.8 (WARN)
unnamed: SW1.2, U12.16 (B3)
unnamed: SW2.2, U10.14 (2B2)
unnamed: TP4.1, X2.1 (EN)
unnamed: TR1.1 (VIN), U11.17 (TX0)
unnamed: U11.20 (RX0), U15.3 (VOUT)
unnamed: R16.1, U16.6 (OUTL)
unnamed: R17.1, U16.7 (OUTR)
VCC: C1.1, C11.1, D1.2 (A), D2.2 (A), J8.2, J9.1, Q1.2 (E), R1.2, R12.1, TR1.2 (VCC), U2.3 (VI), U3.11 (IN-1), U12.20 (VCCB), U13.20 (VCCB), U15.1 (VCC), U17.3 (VI)

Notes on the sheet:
TRS MIDI OUT
TRS MIDI IN
